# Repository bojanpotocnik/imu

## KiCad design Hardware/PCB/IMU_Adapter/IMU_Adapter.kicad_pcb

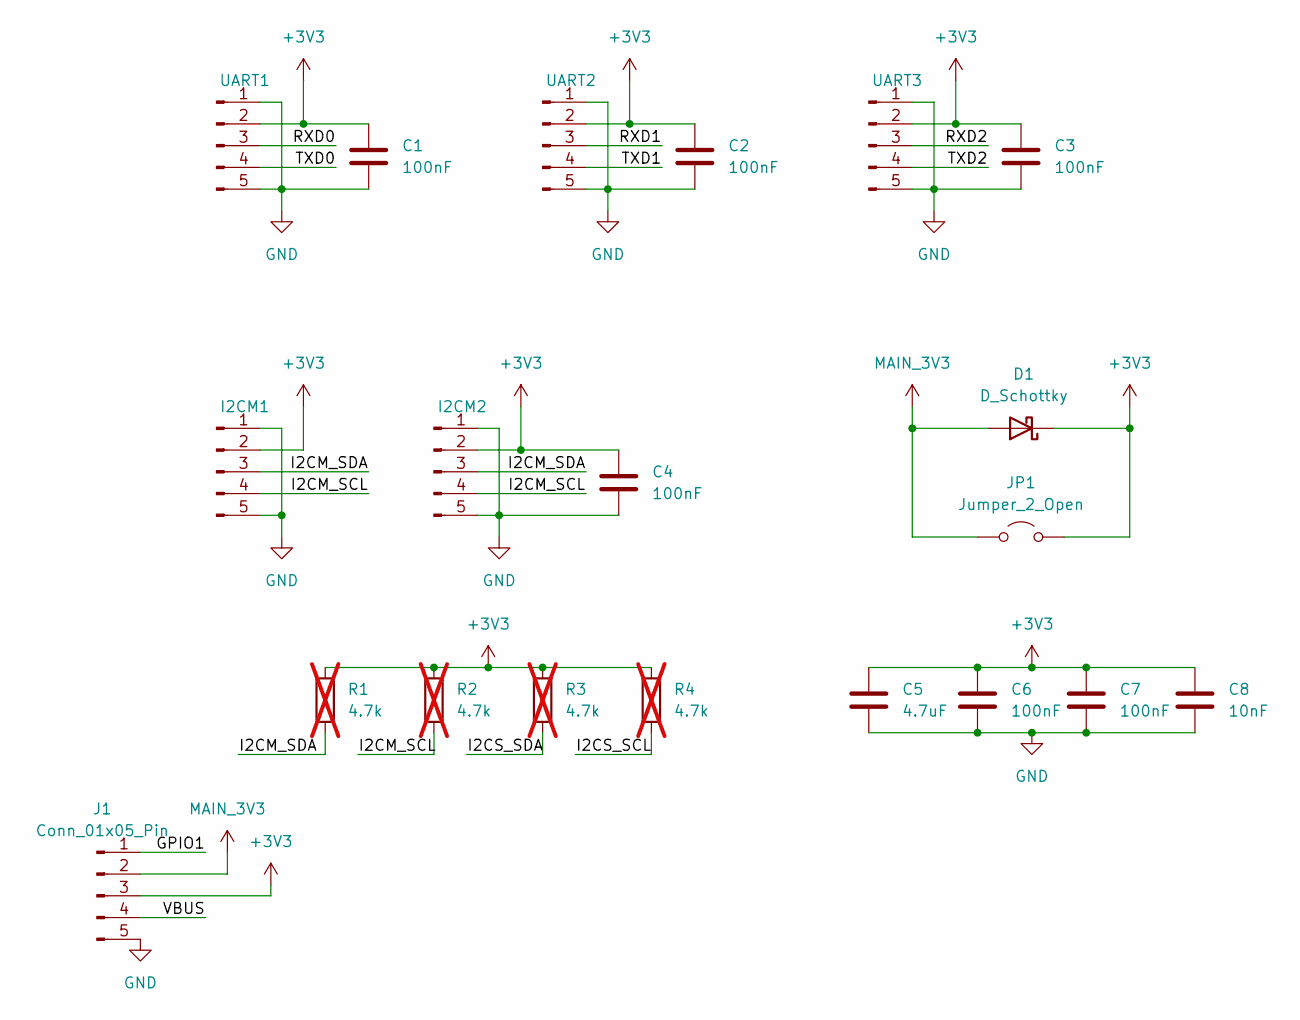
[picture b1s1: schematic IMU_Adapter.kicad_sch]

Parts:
C1, C2, C3, C4, C6, C7: 100nF; C_0805_2012Metric_Pad1.18x1.45mm_HandSolder
C5: 4.7uF; C_0805_2012Metric_Pad1.18x1.45mm_HandSolder
C8: 10nF; C_0805_2012Metric_Pad1.18x1.45mm_HandSolder
D1: D_Schottky; D_SMA_Handsoldering
I2CM1, I2CM2: Conn_01x05_Pin; JST_SH_BM04B-SRSS-TB_1x04-1MP_P1.00mm_Vertical
J1: Conn_01x05_Pin; PinHeader_1x05_P1.27mm_Horizontal
JP1: Jumper_2_Open; PinHeader_1x02_P2.54mm_Horizontal
R1, R2, R3, R4: 4.7k; R_0805_2012Metric_Pad1.20x1.40mm_HandSolder; not fitted
UART1, UART2, UART3: Conn_01x05_Pin; JST_SH_BM04B-SRSS-TB_1x04-1MP_P1.00mm_Vertical

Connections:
+3V3: C1.1, C2.1, C3.1, C4.1, C5.1, C6.1, C7.1, C8.1, D1.1 (K), I2CM1.2, I2CM2.2, J1.3, JP1.2 (B), R1.1, R2.1, R3.1, R4.1, UART1.2, UART2.2, UART3.2; also elsewhere on the board
/GPIO1: J1.1; also elsewhere on the board
/I2CM_SCL: I2CM1.4, I2CM2.4, R2.2; also elsewhere on the board
/I2CM_SDA: I2CM1.3, I2CM2.3, R1.2; also elsewhere on the board
/I2CS_SCL: R4.2; also elsewhere on the board
/I2CS_SDA: R3.2; also elsewhere on the board
/RXD0: UART1.3; also elsewhere on the board
/RXD1: UART2.3; also elsewhere on the board
/RXD2: UART3.3; also elsewhere on the board
/TXD0: UART1.4; also elsewhere on the board
/TXD1: UART2.4; also elsewhere on the board
/TXD2: UART3.4; also elsewhere on the board
/VBUS: J1.4; also elsewhere on the board
GND: C1.2, C2.2, C3.2, C4.2, C5.2, C6.2, C7.2, C8.2, I2CM1.1, I2CM1.5, I2CM2.1, I2CM2.5, J1.5, UART1.1, UART1.5, UART2.1, UART2.5, UART3.1, UART3.5; also elsewhere on the board
MAIN_3V3: D1.2 (A), J1.2, JP1.1 (A)

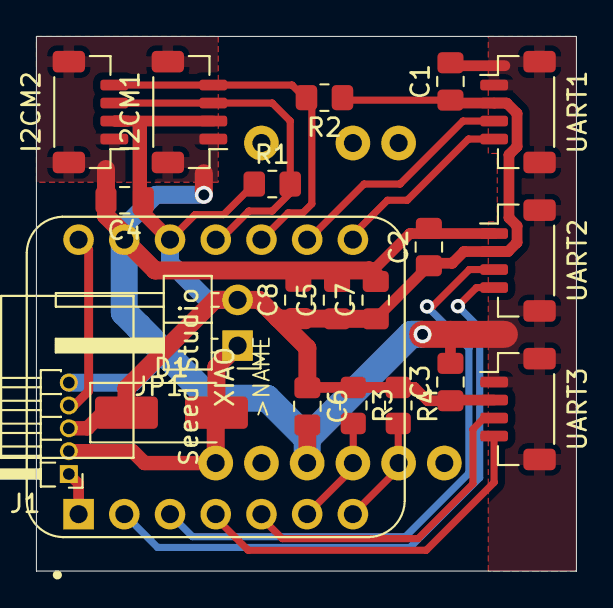
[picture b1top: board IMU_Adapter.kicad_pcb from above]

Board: 2 copper layers, 30.0 x 29.7 mm, 21 parts (0 on the bottom side), 15 nets.

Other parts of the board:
>NAME: >VALUE; XIAO-Generic-Thruhole-14P-2.54-21X17.8MM

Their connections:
+3V3: >NAME.12; also elsewhere on the board
/GPIO1: >NAME.1; also elsewhere on the board
/I2CM_SCL: >NAME.10; also elsewhere on the board
/I2CM_SDA: >NAME.11; also elsewhere on the board
/I2CS_SCL: >NAME.7; also elsewhere on the board
/I2CS_SDA: >NAME.6; also elsewhere on the board
/RXD0: >NAME.9; also elsewhere on the board
/RXD1: >NAME.3; also elsewhere on the board
/RXD2: >NAME.5; also elsewhere on the board
/TXD0: >NAME.8; also elsewhere on the board
/TXD1: >NAME.2; also elsewhere on the board
/TXD2: >NAME.4; also elsewhere on the board
/VBUS: >NAME.14; also elsewhere on the board
GND: >NAME.13; also elsewhere on the board

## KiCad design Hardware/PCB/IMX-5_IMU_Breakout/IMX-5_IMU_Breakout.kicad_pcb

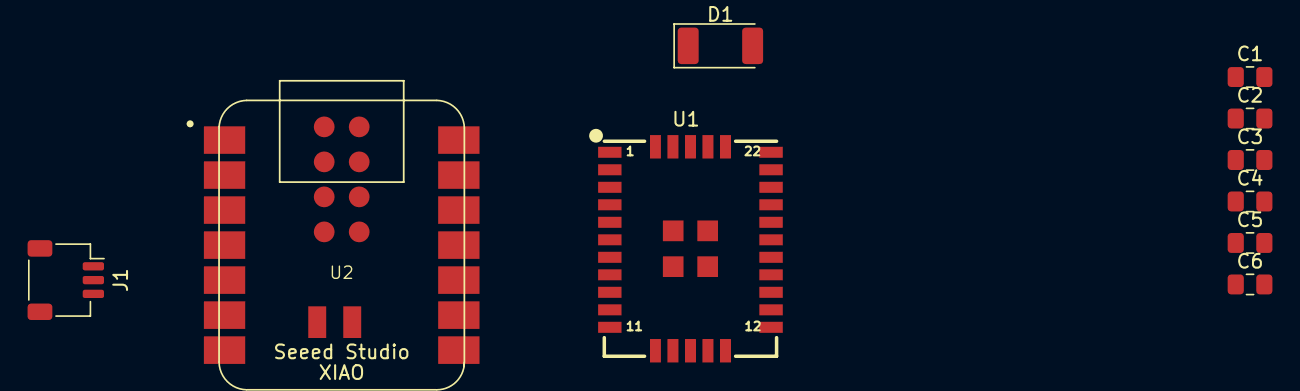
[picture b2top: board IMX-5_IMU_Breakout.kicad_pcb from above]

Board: 2 copper layers, 10 parts (0 on the bottom side), 6 nets, no tracks yet.

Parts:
C1, C2: 100nF; C_0805_2012Metric_Pad1.18x1.45mm_HandSolder
C3: 1uF; C_0805_2012Metric_Pad1.18x1.45mm_HandSolder
C4, C5, C6: 10uF; C_0805_2012Metric_Pad1.18x1.45mm_HandSolder
D1: D_Schottky; D_2010_5025Metric_Pad1.52x2.65mm_HandSolder
J1: Conn_01x04; JST_SH_SM03B-SRSS-TB_1x03-1MP_P1.00mm_Horizontal
U1: IMX; IS-IMX-5.0
U2: Seeed Studio XIAO ESP32 C6; XIAO-ESP32C6-14P-2.54-21X17.8MM

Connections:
+3.3V: C1.1, C2.1, C3.1, C4.1, C5.1, C6.1, D1.1 (K), U1.22 (VCC), U2.12 (3V3)
/SDA: J1.3, U2.5 (SDIO_DATA2/GPIO22/SDA/D4)
GND: C1.2, C2.2, C3.2, C4.2, C5.2, C6.2, J1.1, U1.11 (GND), U1.21 (GND), U2.13 (GND)
unnamed: D1.2 (A), J1.2
unnamed: U1.6 (G6/Rx1/MOSI), U2.3 (LP_GPIO2/GPIO2/A2/D2)
unnamed: U1.7 (G7/Tx1/MISO), U2.4 (SDIO_DATA1/GPIO21/D3)

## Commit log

2024-02-14 Create PlatformIO project configured for ESP32-S3, implement I2C scanner
2024-02-19 Wait for USB Serial to attach, then do single blocking I2C in setup()
2024-02-20 Add library and test for BNO085 sensor
    Euler's angles are printed every 100 ms. 't' can be pressed in the
    serial monitor at any time to perform Tare function.
2024-07-10 Organize the Platformio project to handle multiple subprojects in "apps"
2024-07-10 Optimize Serial baud rate
2024-07-10 Add .clang-format for code formatting
2024-07-11 Add imx5_esp32s3 project
2024-07-11 Add 3 UART instances (for now, just echo the received data)
2024-07-13 Add I2C controller (master) and peripheral (slave) instances
2024-07-14 Fix build failing on Linux because of an invalid cache path
    TEMP variable may not be defined on Linux, and then the resulting path
    was /platformio/build_cache, which is not directly on the root and
    usually not writable. By adding /tmp/ prefix, this works on Linux where
    the resulting path is /tmp/platformio/build_cache, and also on Windows,
    where the path will be %TEMP%/tmp/platformio/build_cache, which is also
    fine.
2024-07-15 Configure pins for IMU Translator PCB
2024-07-15 Add 'inertialsense/inertial-sense-sdk' as a submodule in libs/
2024-07-15 Do not use UART0, which also prints debug messages
2024-07-16 Add driver for IMX-5 IMU
2024-07-16 imu: Read flash configuration during init
2024-07-16 imu: Add option for blocking read of data
2024-07-16 imu: Check command N/ACK
2024-07-16 imu: Fix loop() blocking when more data is received that can be handled
2024-07-17 imu: Read System, AHRS and IMU data
2024-07-17 imu,uart: Increase UART RX buffer to handle data at maximum rates
2024-07-17 imu: Track min/max IMU values
2024-07-17 i2c: Add logging for I2C (assert resets if there are no pull-ups)
2024-07-17 Handle IMX sensor losing connection, reinit when available again
2024-07-17 Send IMU data to the I2C Controller
2024-07-17 Use only I2C peripheral, on I2C controller pins
2025-01-30 Add KiCAD PCB files for IMX-5 breakout board and PCB adapter board
